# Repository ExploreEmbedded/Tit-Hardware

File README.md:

# Tit-Hardware
Hardware design files for Tit with Atmega328pb 

Ever wanted to have two hardware Serial Ports, two SPI, two I2C and more PWM pins on the Arduino Pro Mini? Tit has all of this, and retains the same form factor. Tit uses Atmega328PB at its core. 

Tit, is pin compatible with Arduino Pro Mini, the chip Atmega328pb is software compatible with Atmega328p. Hence all the existing code and libraries should work without any changes. Tit uses higher version of avr-gcc toolchain, we have bundled it up as a package along with additional libraries required to access the extra features. Check the setup section on installing support for the board in the Arduino IDE.

Follow the project at hackaday.io
(https://hackaday.io/project/11558-tit)
Detailed introduction and setup guide at ExploreEmbedded.com
(http://exploreembedded.com/wiki/Tit,_a_supercharged_Arduino_Pro_Mini_with_Atmega328pb)

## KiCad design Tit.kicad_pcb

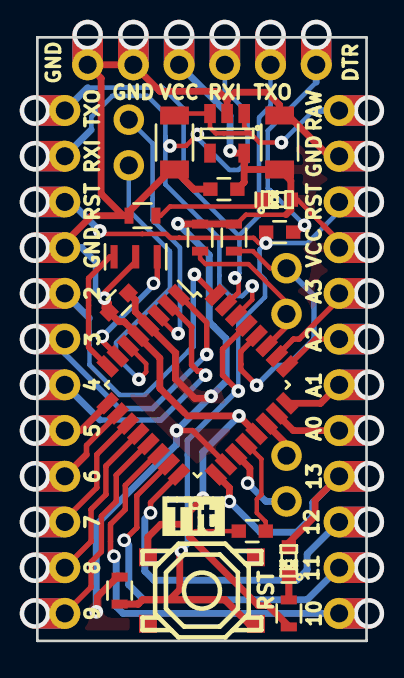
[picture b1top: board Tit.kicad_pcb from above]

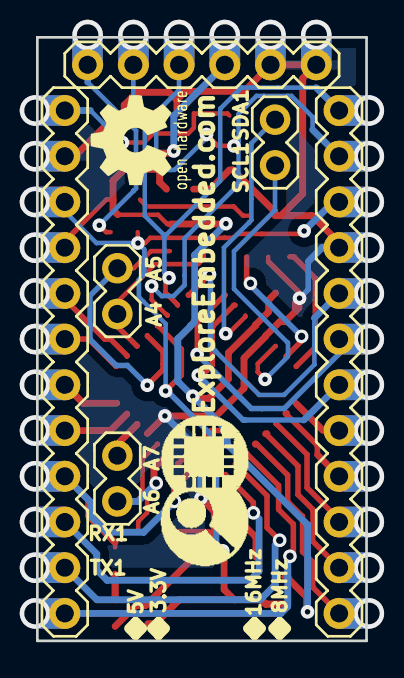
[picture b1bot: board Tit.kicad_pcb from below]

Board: 2 copper layers, 18.3 x 33.5 mm, 26 parts (2 on the bottom side), 34 nets.

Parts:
C1, C2, C3, C4: 0.1uF; C_0603
C5, C8: 10uF; C_1206
D1: Power; LED-0603_NEW
D2: LED; LED-0603_NEW
IC1: ATMEGA328PB; LQFP-32_7x7mm_Pitch0.8mm
IC2: MIC5205; SOT-23-5
LOGO: LOGO (4)
P1: CONN_01X06; Pin_Header_Straight_1x06
P2, P5: CONN_01X12; Pin_Header_Straight_1x12
P3, P4, P6: CONN_01X02; Pin_Header_Straight_1x02
P7: CONN_01X01; LOGO (2)
P8: CONN_01X01; Logo_silk_OSHW_6x6mm
R1, R2: 10K; R_0603
R3, R4: R; R_0603
R5: 470E; R_0603
SW1: RESET; smd_push2
X1: CRYSTAL_SMD; 3Pin_smd_Crstl

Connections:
+5V: C2.1, C4.1, C8.1, D1.1, IC1.4, IC1.18, IC2.5, P1.3, P5.4, R1.1, R3.1, R4.1
/A0: IC1.23, P5.8
/A1: IC1.24, P5.7
/A2: IC1.25, P5.6
/A3: IC1.26, P5.5
/A4: IC1.27, P3.2, R3.2
/A5: IC1.28, P3.1, R4.2
/A6: IC1.19, P6.1
/A7: IC1.22, P6.2
/D2: IC1.32, P2.8
/D3: IC1.1, P2.7
/D4: IC1.2, P2.6
/D5: IC1.9, P2.5
/D6: IC1.10, P2.4
/D7: IC1.11, P2.3
/D8: IC1.12, P2.2
/D9: IC1.13, P2.1
/D10: IC1.14, P5.12
/DTR: C1.2, P1.6
/MISO0: IC1.16, P5.10
/MOSI0: IC1.15, P5.11
/RAW: C5.1, IC2.1, IC2.3, P5.1
/RESET: C1.1, IC1.29, P2.10, P5.3, R1.2, SW1.2
/RXD1: IC1.30, P1.4, P2.11
/SCK0: D2.1, IC1.17, P5.9
/SCL1: IC1.6, P4.2
/SDA1: IC1.3, P4.1
/TXD0: IC1.31, P1.5, P2.12
GND: C2.2, C3.2, C4.2, C5.2, C8.2, IC1.5, IC1.21, IC2.2, P1.1, P1.2, P2.9, P5.2, R2.2, R5.1, SW1.1, X1.3
unnamed: C3.1, IC1.20
unnamed: D1.2, R2.1
unnamed: D2.2, R5.2
unnamed: IC1.7, X1.2
unnamed: IC1.8, X1.1

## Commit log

2016-05-06 Tit Hardware
    Changed file names and added credits, licenses to the files.
2016-05-06 added website link
